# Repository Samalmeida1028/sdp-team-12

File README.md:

# Gathering Live Imagery, Mapping, and Pose Estimation (G.L.I.M.P.S.E.)

The official repository hosting all code written for our robot, Holly, as part of the UMass Amherst Senior Design Project (SDP) 2023-24. Code is written in Python using ROS2 Humble packages for Ubuntu 22.04.3 LTS. 

# Workspace Navigation
Our project consists of 4 workspaces, each having their own documentation as we developed this project. Below is a brief description of each workspace we have, as well as a link to their documentations.

## Control Workspaces
These workspaces contains code that uses ROS2 Control with our robot. ROS2 Control allows us to directly configure our hardware on the robot with ROS2, so there is no need for any dedicated serial code to be written. It receives our navigations commands and converts that to individual wheel speeds, while taking odometry information from the encoders and IMU while navigating. Initial testing was done in the simulated workspace [```controlsim_ws```](https://github.com/Samalmeida1028/sdp-team-12/blob/nav_stable/controlsim_ws/README.md) and then updated with our physical robot in the [```controlphy_ws```](https://github.com/Samalmeida1028/sdp-team-12/blob/nav_stable/controlphy_ws/README.md)

## Navigation Workspaces
These workspaces contain the core code to perform navigation and tracking. Note that we decided to go without using ROS2 Control. We configure the Navigation2 stack here, along with nodes to handle searching for targets, live streaming camera feed, and performing ArUco detection. Initial testing was done in the simulated workspace [```navsim_ws```](https://github.com/Samalmeida1028/sdp-team-12/blob/nav_stable/navsim_ws/README.md) and then updated with our physical robot in the [```navphy_ws```](https://github.com/Samalmeida1028/sdp-team-12/blob/nav_stable/navphy_ws/README.md)

## PCB Documentation 
Documentation about the PCB for our project can be found at [```PCB```](https://github.com/Samalmeida1028/sdp-team-12/tree/nav_stable/PCB)

## ROS2 Installation
Installation scripts for ROS2 Humble and Nav2 in [```rospkginstall```](https://github.com/Samalmeida1028/sdp-team-12/tree/nav_stable/navphy_ws/rospkgsinstall) directory within the [```navphy_ws```](https://github.com/Samalmeida1028/sdp-team-12/blob/nav_stable/navphy_ws/README.md) workspace. Once in that directory, run the following to install ROS2 Humble and Nav2 on your computer:
```
./ros_humble_setup.sh
./ros_humble_nav2_setup.sh
```

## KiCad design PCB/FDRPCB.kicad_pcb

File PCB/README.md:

For our groups PCB we decided to build a custom RP2040 microcontroller which was responsible for handling inputs from the encoders and sending data out to the motor drivers.  The main reason we decided to design a custom RP2040 microcontroller instead of simply using a Raspberry Pi Pico, had to do with us wanting to use widley available connectors to attach and remove motors and encoders from the board.

The Raspberry Pi Foundation publishes an abundant amount of information on the Raspberry Pi Pico microcontroller, including the full schematics and board layout files.  However, these design files are only available in Cadence Allegro, which UMass does not have a licence for - and I do not have the money for.  As a result I was limited to PDF sources, and had to undergo the process of reverse-engineering a Raspberry Pi Pico H in KiCad 7.0.8 utilizing datasheets and other miscelanious PDFs provided by the Raspberry Pi Foundation. 

Below is a 3D render of my board.  This version is much better than the original prototype we had created for our CDR presentation.  Compared to our original prototype, our second and final revision has more efficiently placed items, incorperates components that are more abundantly available, has rounded edges, and an overall more visually pleasing appearance.  I have included the project files which include schematic drawings, PCB layouts, and gerber export files.

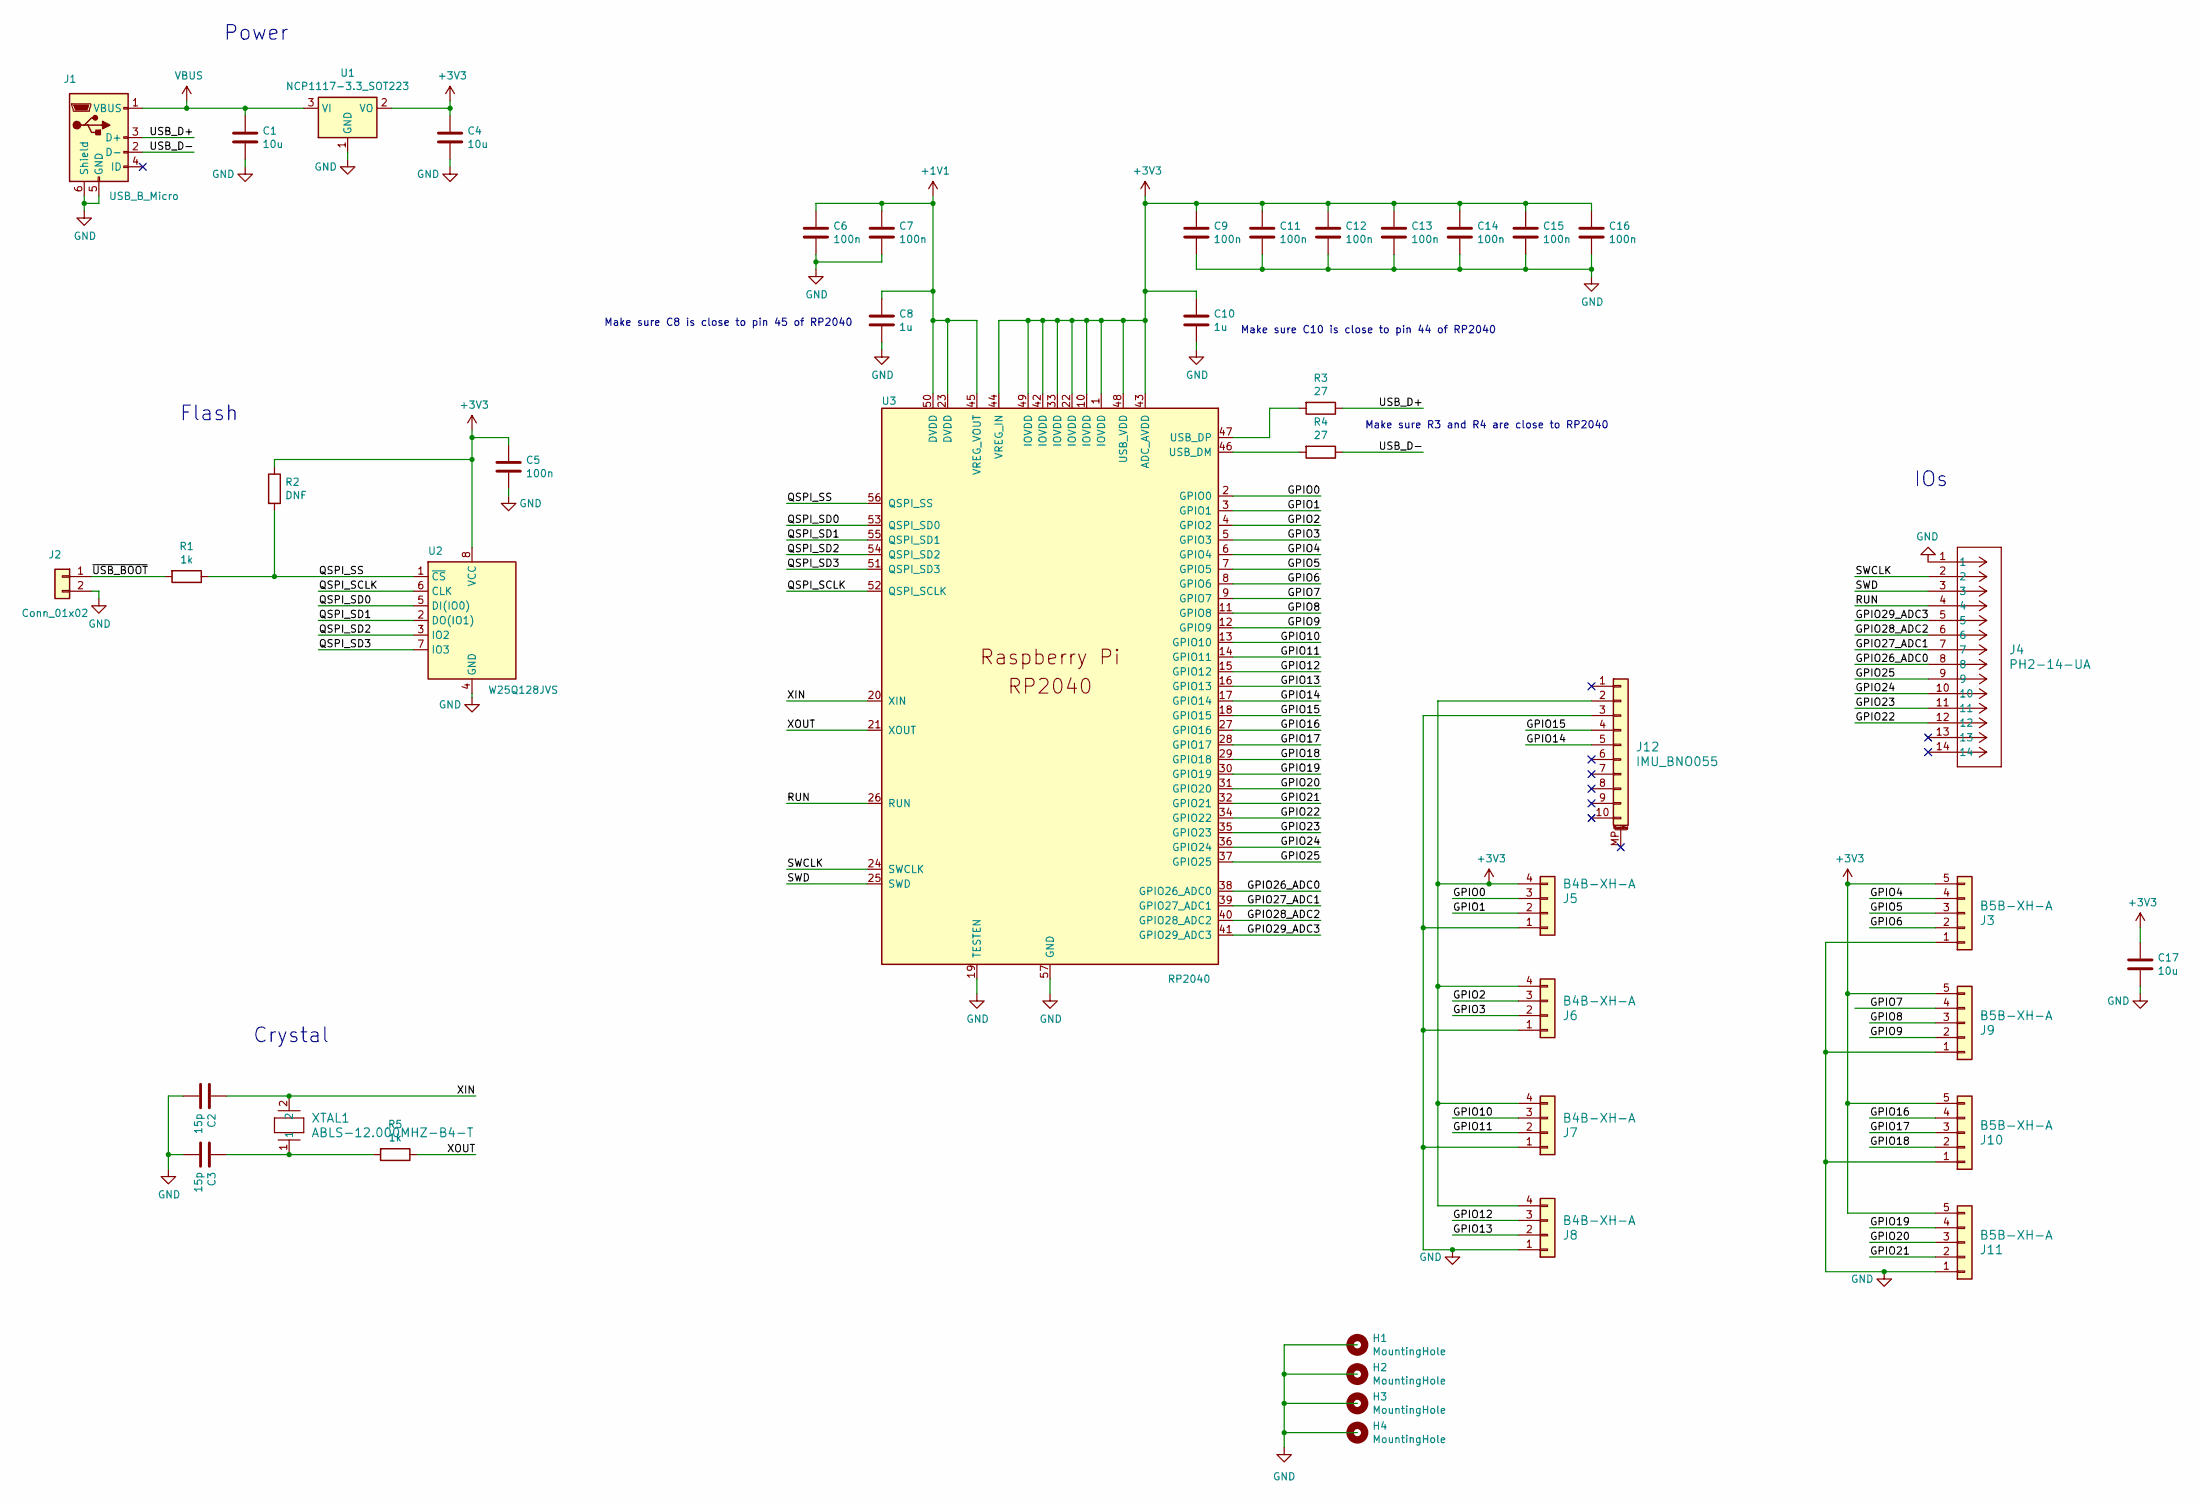
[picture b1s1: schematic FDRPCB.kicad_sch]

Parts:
C1, C4, C17: 10u; C_0805_2012Metric
C2, C3: 15p; C_0402_1005Metric
C5, C6, C7, C9, C11, C12, C13, C14, C15, C16: 100n; C_0402_1005Metric
C8, C10: 1u; C_0402_1005Metric
H1, H2, H3, H4: MountingHole; MountingHole_2.7mm_M2.5
J1: USB_B_Micro; USB_Micro-B_Amphenol_10103594-0001LF_Horizontal_modified
J2: Conn_01x02; PinHeader_1x02_P2.54mm_Vertical
J3, J9, J10, J11: B5B-XH-A; JST_XH_B5B-XH-A_1x05_P2.50mm_Vertical
J4: PH2-14-UA; CONN_PH2-14-UA_ADM
J5, J6, J7, J8: B4B-XH-A; JST_XH_B4B-XH-A_1x04_P2.50mm_Vertical
J12: IMU_BNO055; IMU
R1, R5: 1k; R_0402_1005Metric
R2: DNF; R_0402_1005Metric
R3, R4: 27; R_0402_1005Metric
U1: NCP1117-3.3_SOT223; SOT-223-3_TabPin2
U2: W25Q128JVS; SOIC-8_5.23x5.23mm_P1.27mm
U3: RP2040; RP2040-QFN-56
XTAL1: ABLS-12.000MHZ-B4-T; XTAL_ABLS_ABR

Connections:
+1V1: C6.1, C7.1, C8.1, U3.23 (DVDD), U3.45 (VREG_VOUT), U3.50 (DVDD)
+3V3: C4.1, C5.1, C9.1, C10.1, C11.1, C12.1, C13.1, C14.1, C15.1, C16.1, C17.1, J3.5, J5.4, J6.4, J7.4, J8.4, J9.5, J10.5, J11.5, J12.2, R2.1, U1.2 (VO), U2.8 (VCC), U3.1 (IOVDD), U3.10 (IOVDD), U3.22 (IOVDD), U3.33 (IOVDD), U3.42 (IOVDD), U3.43 (ADC_AVDD), U3.44 (VREG_IN), U3.48 (USB_VDD), U3.49 (IOVDD)
/GPIO0: J5.3, U3.2 (GPIO0)
/GPIO1: J5.2, U3.3 (GPIO1)
/GPIO2: J6.3, U3.4 (GPIO2)
/GPIO3: J6.2, U3.5 (GPIO3)
/GPIO4: J3.4, U3.6 (GPIO4)
/GPIO5: J3.3, U3.7 (GPIO5)
/GPIO6: J3.2, U3.8 (GPIO6)
/GPIO7: J9.4, U3.9 (GPIO7)
/GPIO8: J9.3, U3.11 (GPIO8)
/GPIO9: J9.2, U3.12 (GPIO9)
/GPIO10: J7.3, U3.13 (GPIO10)
/GPIO11: J7.2, U3.14 (GPIO11)
/GPIO12: J8.3, U3.15 (GPIO12)
/GPIO13: J8.2, U3.16 (GPIO13)
/GPIO14: J12.5, U3.17 (GPIO14)
/GPIO15: J12.4, U3.18 (GPIO15)
/GPIO16: J10.4, U3.27 (GPIO16)
/GPIO17: J10.3, U3.28 (GPIO17)
/GPIO18: J10.2, U3.29 (GPIO18)
/GPIO19: J11.4, U3.30 (GPIO19)
/GPIO20: J11.3, U3.31 (GPIO20)
/GPIO21: J11.2, U3.32 (GPIO21)
/GPIO22: J4.12, U3.34 (GPIO22)
/GPIO23: J4.11, U3.35 (GPIO23)
/GPIO24: J4.10, U3.36 (GPIO24)
/GPIO25: J4.9, U3.37 (GPIO25)
/GPIO26_ADC0: J4.8, U3.38 (GPIO26_ADC0)
/GPIO27_ADC1: J4.7, U3.39 (GPIO27_ADC1)
/GPIO28_ADC2: J4.6, U3.40 (GPIO28_ADC2)
/GPIO29_ADC3: J4.5, U3.41 (GPIO29_ADC3)
/QSPI_SCLK: U2.6 (CLK), U3.52 (QSPI_SCLK)
/QSPI_SD0: U2.5 (DI(IO0)), U3.53 (QSPI_SD0)
/QSPI_SD1: U2.2 (DO(IO1)), U3.55 (QSPI_SD1)
/QSPI_SD2: U2.3 (IO2), U3.54 (QSPI_SD2)
/QSPI_SD3: U2.7 (IO3), U3.51 (QSPI_SD3)
/QSPI_SS: R1.1, R2.2, U2.1 (~CS), U3.56 (QSPI_SS)
/RUN: J4.4, U3.26 (RUN)
/SWCLK: J4.2, U3.24 (SWCLK)
/SWD: J4.3, U3.25 (SWD)
/USB_D+: J1.3 (D+), R3.1
/USB_D-: J1.2 (D-), R4.1
/XIN: C2.1, U3.20 (XIN), XTAL1.2
/XOUT: R5.1, U3.21 (XOUT)
/~USB_BOOT: J2.1, R1.2
GND: C1.2, C2.2, C3.2, C4.2, C5.2, C6.2, C7.2, C8.2, C9.2, C10.2, C11.2, C12.2, C13.2, C14.2, C15.2, C16.2, C17.2, J1.5 (GND), J1.6 (Shield), J2.2, J3.1, J4.1, J5.1, J6.1, J7.1, J8.1, J9.1, J10.1, J11.1, J12.3, U1.1 (GND), U2.4 (GND), U3.19 (TESTEN), U3.57 (GND)
unnamed: C3.1, R5.2, XTAL1.1
unnamed: R4.2, U3.46 (USB_DM)
unnamed: R3.2, U3.47 (USB_DP)
VBUS: C1.1, J1.1 (VBUS), U1.3 (VI)

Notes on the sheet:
IOs
Power
Crystal
Make sure C8 is close to pin 45 of RP2040
Make sure C10 is close to pin 44 of RP2040
Make sure R3 and R4 are close to RP2040
Flash

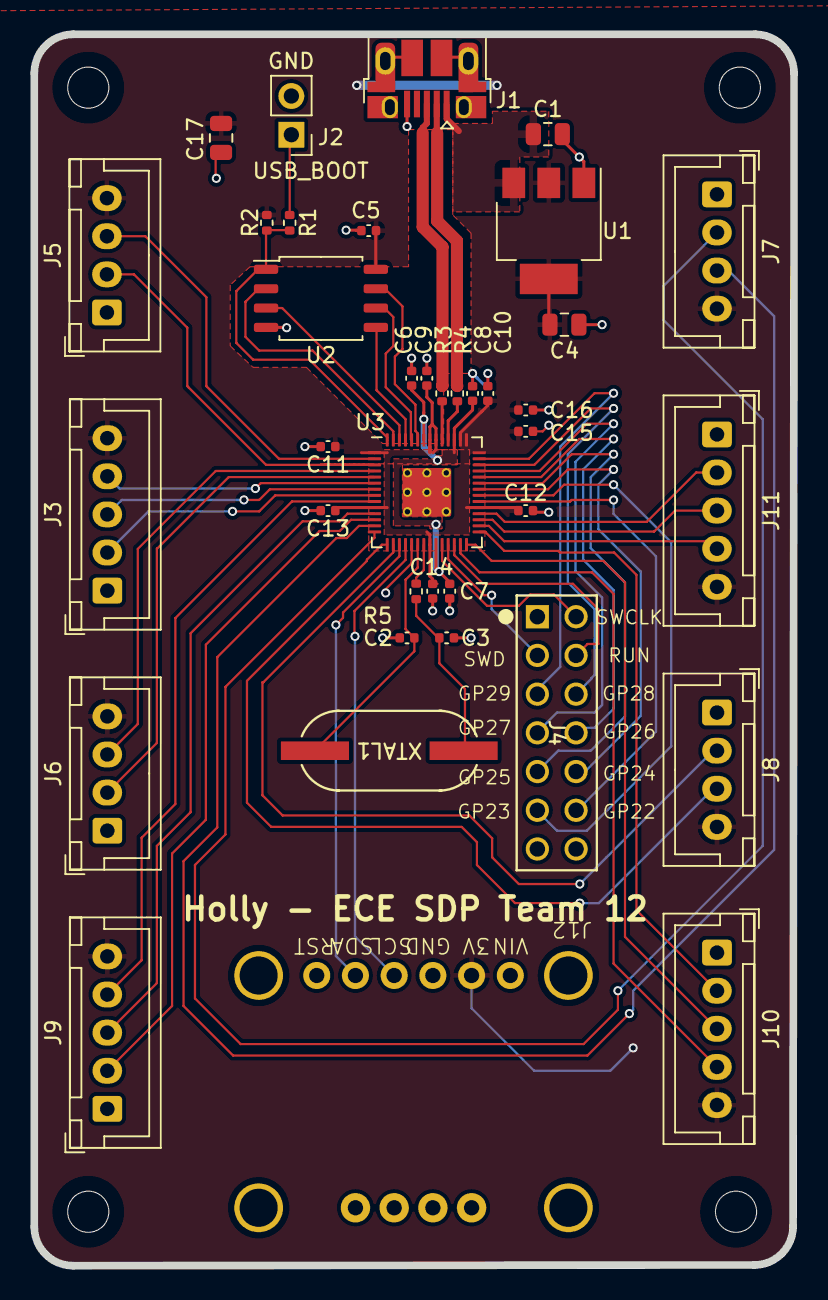
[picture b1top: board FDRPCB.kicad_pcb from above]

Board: 2 copper layers, 49.8 x 80.8 mm, 42 parts (0 on the bottom side), 51 nets.

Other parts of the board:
H2#2: MountingHole; MountingHole_2.7mm_M2.5

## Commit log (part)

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2023-10-24 set up code in ros2 package
2023-10-24 created a ros2 package
2023-10-26 Updated and added docs to package
2023-10-26 deleted some stuff
2023-10-26 created a python package
2023-10-26 added all documentation for finishing
2023-10-26 sample build of package
2023-10-26 updating paths
2023-10-26 added example package
2023-10-26 packages are working
2023-10-26 installed all packages
2023-10-27 got everything working package wise
2023-10-27 created ros2 package for navigation
2023-10-27 ros2 package for navigation initialized
2023-10-27 update build
2023-10-28 got rviz/gazebo sim working
2023-10-28 set up URDF and RViz files
2023-10-28 built package with URDF and RViz files
2023-10-28 set up navigation package
2023-10-29 remaking branch
2023-10-29 setup cmake package for navigation
2023-10-29 reinitalized branch
2023-10-29 set up python package and developed
2023-10-29 updated README for rough doc
2023-10-29 final changes 10/29/23
2023-10-30 added some packages
2023-10-30 adding image streaming
2023-10-30 editing
2023-10-30 added nav2 simulation
2023-10-31 revert back to 10/29/23 when it worked
2023-11-01 restructuring
2023-11-01 detection and pose estimation working in ros
2023-11-01 this doesnt work rn
2023-11-01 adding some imports
2023-11-01 logs
2023-11-01 not working
2023-11-01 working again
2023-11-02 got SLAM working, static map still no work
2023-11-05 added scripts to test out
2023-11-06 added set up for nodes. Work in progress
2023-11-06 added things to install shell script
2023-11-06 added setup files for installations
2023-11-06 added navigator package to test out
2023-11-06 set up all packages for navigation
2023-11-07 tilt pan working code
2023-11-07 making it work on linux
2023-11-07 work in progress
2023-11-07 added more tracking
2023-11-07 base packages workspace
2023-11-07 progress track
2023-11-08 got it working!!!
2023-11-08 deliverable 2 is working
2023-11-08 updated files
2023-11-08 final changes 11/7/23
2023-11-08 more calibration
2023-11-08 added more features and tuned the PID a bit
2023-11-08 added boot.py
2023-11-08 updated files 11/8/23
2023-11-08 added rudimentary pico code
2023-11-08 added serial comms for mmotor control
2023-11-08 updates from 11/8/23
2023-11-08 Rename nav_env.launch.py to nav_simulated.launch.py
2023-11-09 work transfer to linux laptop
2023-11-10 work in progress 11/9/23
2023-11-11 can send forward and backward command with keys
2023-11-11 got the navigation nodes working
2023-11-12 put together tracking and navigation
2023-11-12 keys increase or decrease velocity vector
2023-11-13 work in progress 11/12
2023-11-13 motors are moving!!
2023-11-13 added both together
2023-11-13 added some cool stuff
2023-11-13 added the pid stuff
2023-11-13 work 11/13
2023-11-13 arjuns last session
2023-11-14 work 11/14/23
2023-11-14 added the SDP 12 URDF
2023-11-14 to do SDF file 11/14/23
2023-11-14 added teleop
2023-11-14 work in progress 11/14/23
2023-11-14 changed just the com port
2023-11-14 added python script for teleop for pc
2023-11-14 added other files
2023-11-14 work
2023-11-15 got differential + holonomic working
2023-11-15 work in progress 11/15/23
2023-11-15 what
2023-11-15 working in empty world but no real lidar data
2023-11-15 set up for odometry publishing
2023-11-15 added pico code for working odom
2023-11-15 got lidar odometry set up
2023-11-15 figure out why ekf does not publish tf
2023-11-16 mapping with real lidar working!!!
2023-11-16 SLAM working!!!
2023-11-16 integrated everything to a launch file
2023-11-16 to add in nav stack
2023-11-16 putting nav stack
2023-11-16 to do nav stack integration with SLAM
2023-11-16 final changes for 11/15/23
2023-11-17 setting checkpoint for navigation
2023-11-17 navigation working!! Checkpoint 1
2023-11-17 navigation all set up! Fine tuning todo
2023-11-17 set checkpoint for future
2023-11-17 set up lidar and wheel odom fusion
2023-11-17 todo encoder to odom conversion
2023-11-18 need to fix navigation planner. Checkpoint
2023-11-19 file changes
2023-11-21 narrowed down issue to costmap params
2023-11-22 added encoder stuff
2023-11-22 refactoring
2023-11-22 added beginning of documentation for project
2023-11-22 navigation works!!
2023-11-24 changed links
2023-11-26 confirmed nav2 is working consistently
2023-11-27 working without lidar odom. Work in progress
2023-11-28 better slam
2023-11-28 work in progress 11/28/23
2023-11-29 todo: make path following correctly
2023-11-29 nav simulated check in working again
2023-11-30 work in progress 11/29
2023-11-30 to be continued
2023-11-30 this works.
2023-11-30 checkpoint 1
2023-11-30 work 11/29/23
2023-11-30 checkpoint 2
2023-11-30 added teleop capability for rviz
2023-11-30 odom is almost functional, need to fix motor
2023-11-30 nav works
2023-11-30 mroe changes
2023-11-30 directory cleanups for nav working
2023-12-01 changing radius
2023-12-01 started tweaking odom, trying to get it closer
2023-12-01 smoother working
2023-12-01 checkpoint 4
2023-12-02 added videos
2023-12-02 physical navigation only working
2023-12-02 nav simulated only working
2023-12-04 port docs
2023-12-04 got video for target tracking
2023-12-06 test
2023-12-06 commented out smoother for now
2023-12-09 Update nav2_params.yaml
    recoveries need to be tested
2023-12-09 Update navigation_launch.py
    removed recoveries_server
2023-12-09 to be tested 12/9
2023-12-10 test out behaviors
2023-12-11 need to make recoveries work
2023-12-16 debugging behaviors
2023-12-16 research into ros2_control
2023-12-16 clone into branch
2023-12-16 needs testing
2023-12-16 working nav simulated branch
2023-12-16 set up simulation for using ros2_control
2023-12-20 got ros2_control working on simulation
2023-12-22 changed to robo holly
2023-12-24 some small changes
2023-12-24 added physical robot ros2 control packages
2023-12-29 redone changes
2023-12-29 added diffbot from ros2 control
2024-01-10 bruh
2024-01-27 recoveries are triggering
2024-02-04 work in progress 2/3/24
2024-02-04 work in progress 2/4/24
2024-02-04 fixed map jump errors. Need to figure out turning
2024-02-05 messing with movement commands
2024-02-05 work in progress 2/5/24
2024-02-05 updates 2/5/24
2024-02-07 working navigation and good odometry 2/7
2024-02-07 electrical issue identified. Progress 2/7
2024-02-07 nav and target
2024-02-08 integration checkpoint 1 2/8/24
2024-02-08 integration testing checkpoint 1
2024-02-08 integration checkpoint 2 2/8/24
2024-02-09 fix goal pose. work in progress 2/8/24
2024-02-10 odometry is not correct. fix. work 2/9/24
2024-02-10 odometry is really good and works with all
2024-02-10 latest stable releases
2024-02-10 working 2/10/24
2024-02-12 phi works better now
2024-02-12 checkpoint 1 2/12/24
2024-02-13 checkpoint working 2/13/24
2024-02-13 search behavior working checkpoint 1
2024-02-14 checkpoint for search behaviors 2/14/23
2024-02-15 search behaviors working checkpoint 1
2024-02-20 checkpoint 2/20/24
2024-02-21 reversing a lot better now, but still changes directions
2024-02-21 updated nav2_params.yaml
2024-02-22 robot is reversing longer distances now
2024-02-24 work 2/23/24
2024-02-24 checkpoint updated URDF and functionality
2024-02-24 update URDF checkpoint 2
2024-02-24 create physical workspace
2024-02-24 updated physical workspace
2024-02-24 merged nav workspaces
2024-02-26 backup pico code
2024-02-29 update to new chassis. Checkpoint 1
2024-03-04 update to new robot 3/4/23
2024-03-04 update search targets wait time
2024-03-04 tested 3/4/24
2024-03-05 update pico code and testing
2024-03-06 work 3/5/24
2024-03-06 working 3/5/24 fixed git tree
2024-03-06 integration and searching working
2024-03-07 working 3/6/24
2024-03-08 added recording capability
2024-03-10 recording working 3/8/24
2024-03-12 work 3/11/24
2024-03-12 arguments to launch files
2024-03-12 work for 3/12/24
2024-03-16 work in progress 3/16
2024-03-17 target publishing updated 3/16
2024-03-17 new search targets capability setup
2024-03-18 fully functional target publishing 3/18/24
2024-03-18 to be tested 3/18/24
2024-03-21 updated with GUI 3/21/24
2024-03-21 updated gui to do parallel execution
2024-03-21 corrected update for parallel exec 3/21/24
2024-03-22 documentation on ssh X forwarding
2024-03-23 NLP capability working and in GUI
2024-03-24 work in progress 3/24/24
2024-03-25 tuning in progress 3/25/24
2024-03-26 lidar filter implemented
2024-03-26 work in progress 3/26/24
2024-03-27 working 3/27/24
2024-03-27 Revert "testing on laptop 3/27/24"
    This reverts commit 09b6779bfb77d974a82a51fcff96725ef05a3686.
2024-03-27 updated full test on NUC 3/27/24
2024-03-28 Added GUI and lot more changes 3/28/24
2024-03-28 new chassis upgrade and work in progress 3/28/24
2024-03-29 work in progress 3/29/24
2024-03-30 assisted teleop + working 3/30/24
2024-03-30 updated assisted teleop + new cam params
2024-03-30 target tracking updates
2024-03-30 update changelog to 3/30/24
2024-03-30 checkpoint 1 3/30/24
2024-03-30 bluetooth connect script for NLP
2024-03-30 nlp tuning
2024-03-31 testing
2024-03-31 new testing updates
2024-04-03 changes part 1 4/3/24
2024-04-03 changes part 2 4/3/24
2024-04-04 updates 4/3/24
2024-04-04 backup target tracking pico code
2024-04-04 update gitignore
2024-04-04 checkpoint 1 4/4/24
2024-04-04 added image pub with audio recording capability
2024-04-04 checkpoint 2 4/4/24
2024-04-04 fixed bluetooth audio issue
2024-04-04 update paths for control ws
2024-04-05 video capture working 4/4/24
2024-04-05 testing working 4/4/24
2024-04-05 checkpoint 4/5/24
2024-04-06 working target pub 4/6/24
2024-04-06 updates for using audio
2024-04-06 checkpoint working drive 4/6/24
2024-04-07 tuning navigation 4/7/24
2024-04-07 added PCB working 4/7/24
2024-04-08 work in progress tracking 4/7/24
2024-04-08 individual target video and audio recording working
2024-04-08 updates 4/8/24
2024-04-08 slowing down audio
2024-04-09 checkpoint 4/9/24
2024-04-09 video splitting capability 4/9/24
2024-04-09 updates 4/9/24
2024-04-09 real time test results
2024-04-11 full tests in drive 4/10/24
2024-04-11 fixed bug with wavefile writing thread
2024-04-12 testing working 4/12/24
2024-04-16 navigation back to working well 4/16/24. Checkpoint 1
2024-04-16 full test working 4/16/24. Checkpoint 2
2024-04-16 full test smoothed working. Checkpoint 4
2024-04-16 backup pico codes
2024-04-17 audio works over rdp 4/16/24 final changes
2024-04-17 checkpoint 1 4/17/24
2024-04-17 checkpoint 2 4/17/24
2024-04-17 camera search working with nav 4/17/24
2024-04-18 testing 4/18/24
2024-04-18 checkpoint 2 4/18/24
2024-04-19 audio in sync with real time checkpoint 3 4/18/24
2024-04-19 working 4/18/24
2024-04-19 working with live stream 4/18/24
2024-04-19 no live stream. Just base recording and what not. Check 1
2024-04-19 checkpoint 2 4/19/24
2024-04-20 added demo day stuff
2024-04-20 work in progress 4/19/24
2024-04-20 checkpoint 1 testing 4/20/24
2024-04-21 checkpoint 1 4/21/24
2024-04-21 checkpoint 2 4/21/24
2024-04-22 testing 4/21/24
2024-04-22 final testing 4/21/24
2024-04-22 checkpoint 1 working 4/22/24
2024-04-23 sam changes 4/22/24
2024-04-23 checkpoint 1 4/23/24 updated GUI
2024-04-23 checkpoint 2 4/23/24
2024-04-24 FPR testing changes 4/24/24
2024-04-24 saved changes 4/24/24
2024-04-24 refactoring main
2024-04-24 updating scipts with new paths
2024-04-25 updates 4/25/24
2024-04-25 test update
2024-04-25 updated for 4/25/24
2024-04-25 checkpoint 2 4/25/24
2024-04-25 update bt
2024-04-26 got everything updated to before NUC died
2024-04-26 laptop version of nav_stable
2024-04-26 checkpoint pre FPR 1
2024-04-26 checkpoint 2 pre FPR
2024-04-26 final checkpoint for FPR
2024-04-26 FPR final changes
2024-04-27 updates to cycle targets
2024-04-30 adding macros for robot demo day
2024-04-30 checkpoint working 4/30/24
2024-05-02 with laptop. Checkpoint 5/1/24
2024-05-02 checkpoint working 5/2/24
2024-05-02 updated with neopixel
2024-05-02 added new lidar stuff
2024-05-03 checkpoint working pre demo day
2024-05-03 checkpoint 2 pre demo day
2024-05-03 checkpoint 3 pre demo day
2024-05-03 checkpoint 4 pre demo day
2024-05-03 checkpoint 5 pre demo day
2024-05-03 demo day 1 dchanges
2024-05-03 changes 5/3/24
2024-05-03 tuning based off demo day performance
2024-05-03 final changes 5/3/24
2024-05-04 final demo day changes 5/4/24
2024-05-10 final changes 5/10/24
